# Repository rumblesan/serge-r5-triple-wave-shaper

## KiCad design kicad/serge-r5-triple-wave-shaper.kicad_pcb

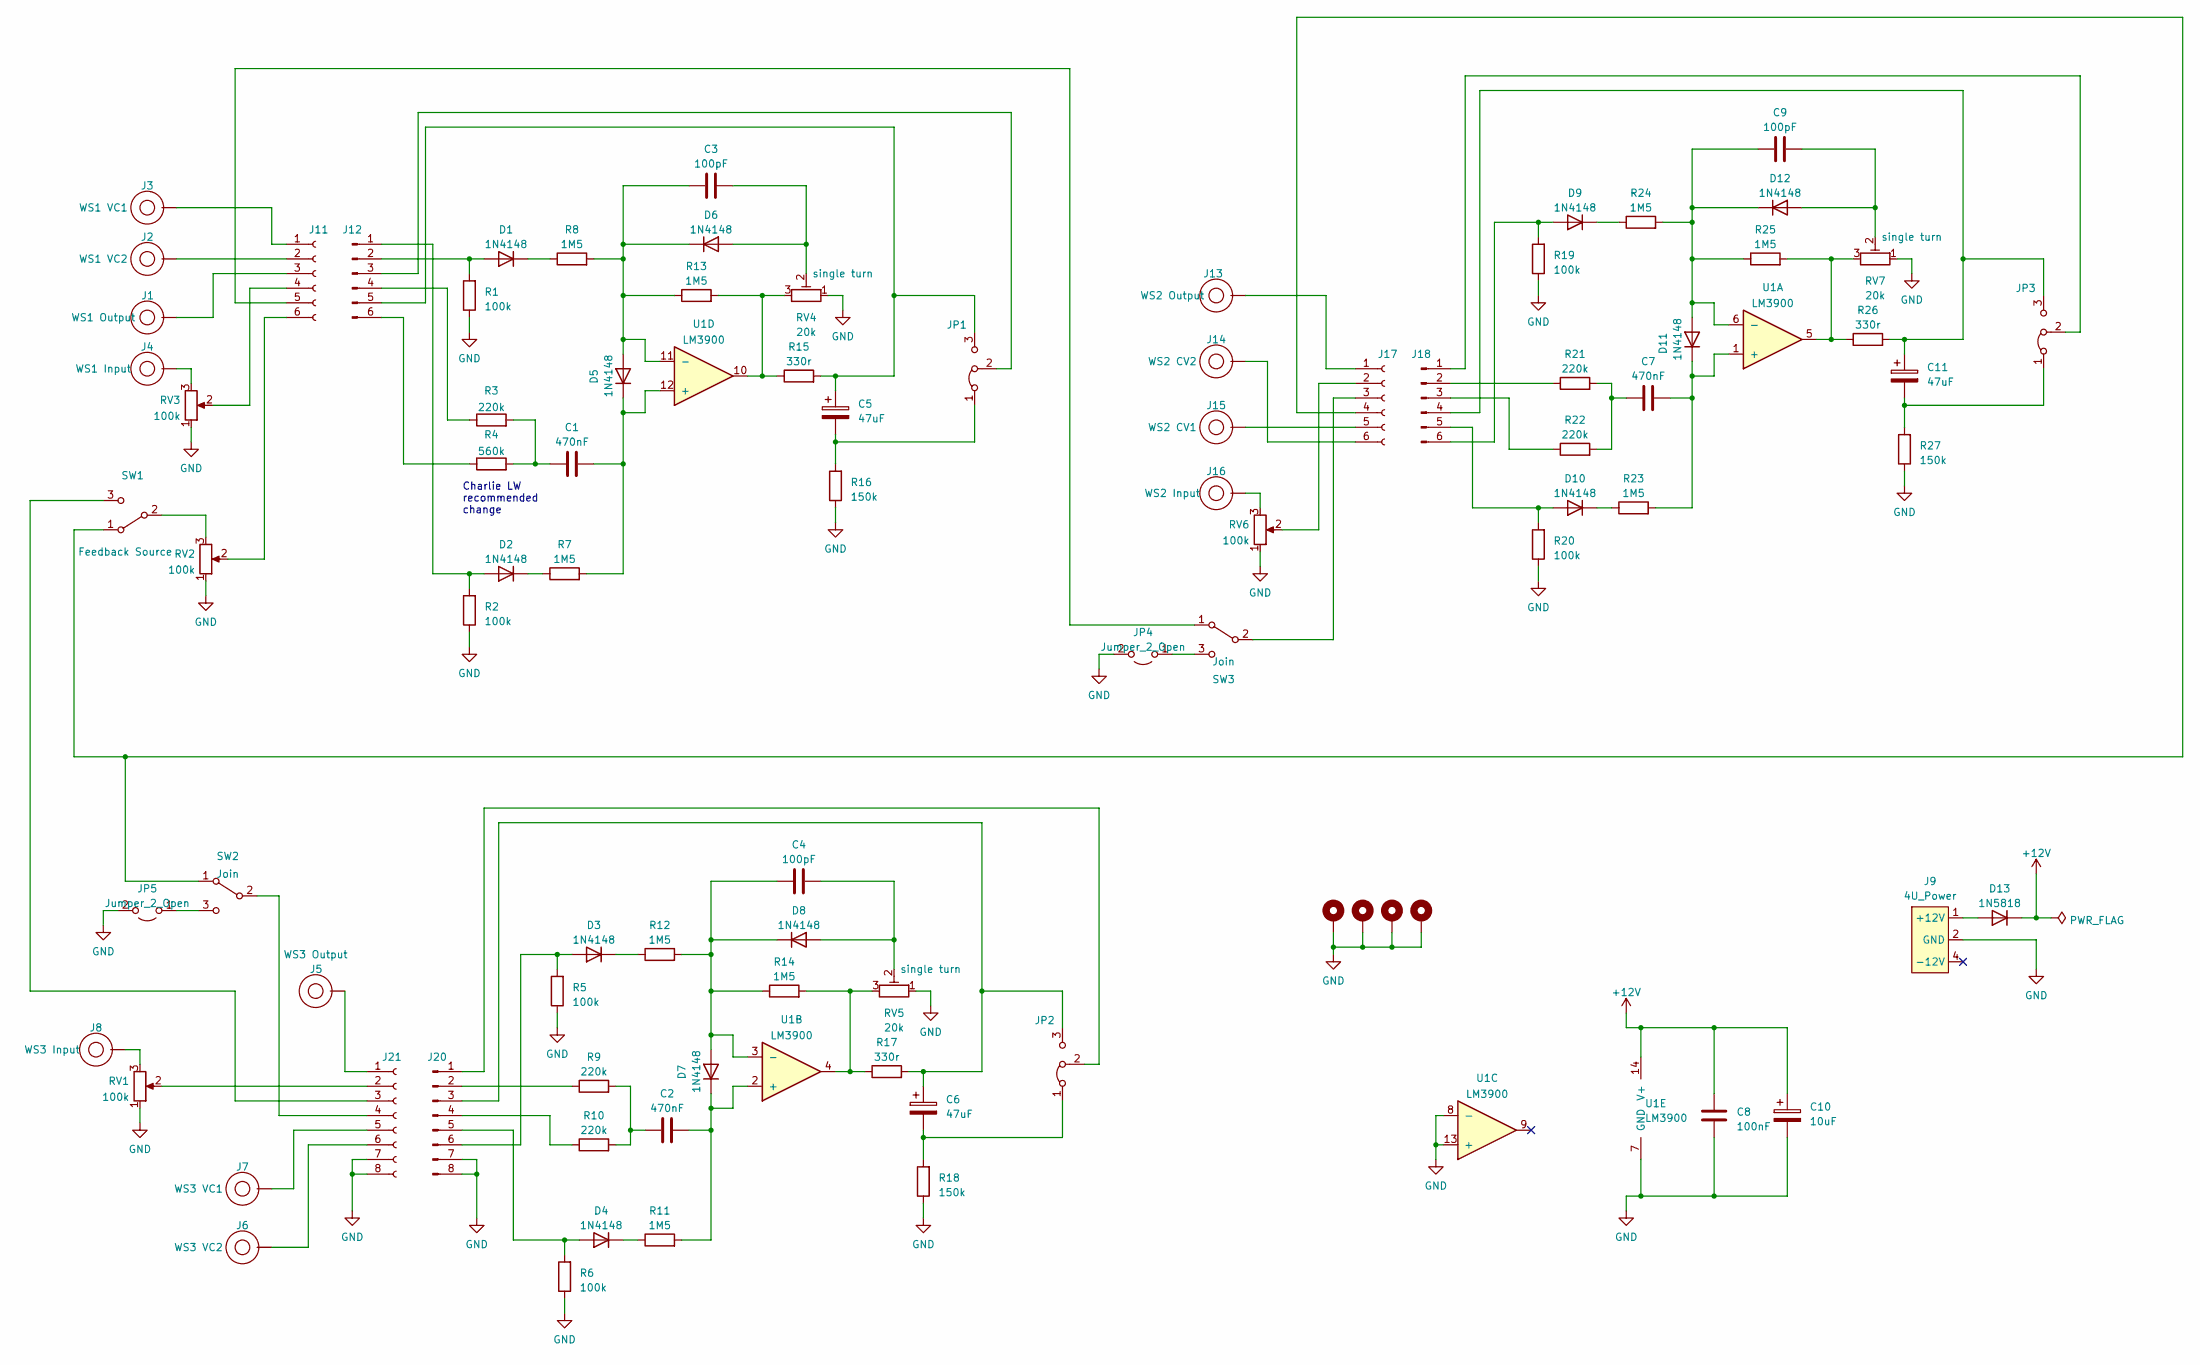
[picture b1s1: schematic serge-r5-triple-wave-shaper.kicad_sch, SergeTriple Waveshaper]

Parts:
C1, C2, C7: 470nF; C_Rect_L7.2mm_W8.5mm_P5.00mm_FKP2_FKP2_MKS2_MKP2; Tolerance 5%
C3, C4, C9: 100pF; C_Rect_L7.0mm_W3.5mm_P5.00mm; Tolerance 5%
C5, C6, C11: 47uF; CP_Radial_D5.0mm_P2.00mm; Tolerance 20%; Voltage 50v
C8: 100nF; C_Rect_L7.0mm_W3.5mm_P5.00mm; Tolerance 5%
C10: 10uF; CP_Radial_D5.0mm_P2.00mm; Tolerance 20%; Voltage 50v
D1, D2, D3, D4, D5, D6, D7, D8, D9, D10, D11, D12: 1N4148; D_DO-35_SOD27_P7.62mm_Horizontal
D13: 1N5818; D_DO-41_SOD81_P10.16mm_Horizontal
H1, H2, H3, H4: MountingHole_Pad; MountingHole_3.2mm_M3_Pad
J1, J2, J3, J4, J5, J6, J7, J8, J13, J14, J15, J16: Banana Socket PanelMount; BananaJack_THT_JohnsonCinch_108-09
J9: 4U_Power; 4u_Power_Molex_KK-254_P2.54mm
J11, J17: Conn_01x06_Female; PinSocket_1x06_P2.54mm_Vertical
J12, J18: Conn_01x06_Male; PinHeader_1x06_P2.54mm_Vertical
J20: Conn_01x08_Pin; PinHeader_1x08_P2.54mm_Vertical
J21: Conn_01x08_Socket; PinSocket_1x08_P2.54mm_Vertical
JP1, JP2, JP3: Jumper_3_Bridged12; PinHeader_1x03_P2.54mm_Vertical
JP4, JP5: Jumper_2_Open; SolderJumper-2_P1.3mm_Open_Pad1.0x1.5mm
R1, R2, R5, R6, R19, R20: 100k; R_Axial_DIN0207_L6.3mm_D2.5mm_P10.16mm_Horizontal; Tolerance 1%
R3, R9, R10, R21, R22: 220k; R_Axial_DIN0207_L6.3mm_D2.5mm_P10.16mm_Horizontal; Tolerance 1%
R4: 560k; R_Axial_DIN0207_L6.3mm_D2.5mm_P10.16mm_Horizontal; Tolerance 1%
R7, R8, R11, R12, R13, R14, R23, R24, R25: 1M5; R_Axial_DIN0207_L6.3mm_D2.5mm_P10.16mm_Horizontal; Tolerance 1%
R15, R17, R26: 330r; R_Axial_DIN0207_L6.3mm_D2.5mm_P10.16mm_Horizontal; Tolerance 1%
R16, R18, R27: 150k; R_Axial_DIN0207_L6.3mm_D2.5mm_P10.16mm_Horizontal; Tolerance 1%
RV1, RV2, RV3, RV6: 100k; Potentiometer_Alpha_RD901F-40-00D_Single_Vertical
RV4, RV5, RV7: 20k; Potentiometer_THT_Bourns_3306P_Vertical
SW1, SW2, SW3: SW_SPDT; Toggle_Switch_100SP-M2
U1: LM3900; DIP-14_W7.62mm_Socket

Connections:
+12V: C8.1, C10.1, D13.1 (K), U1.14 (V+)
GND: C8.2, C10.2, H1.1, H2.1, H3.1, H4.1, J9.2 (GND), J9.3 (GND), J20.7, J20.8, J21.7, J21.8, JP4.2 (B), JP5.2 (B), R1.1, R2.1, R5.1, R6.1, R16.1, R18.1, R19.1, R20.1, R27.1, RV1.1, RV2.1, RV3.1, RV4.1, RV5.1, RV6.1, RV7.1, U1.7 (GND), U1.8 (-), U1.13 (+)
unnamed: C1.1, R3.2, R4.2
unnamed: C2.1, R9.2, R10.2
unnamed: C7.1, R21.2, R22.2
unnamed: D1.2 (A), J12.2, R1.2
unnamed: D1.1 (K), R8.1
unnamed: D2.2 (A), J12.1, R2.2
unnamed: D2.1 (K), R7.1
unnamed: D3.2 (A), J20.6, R5.2
unnamed: D3.1 (K), R12.1
unnamed: D4.2 (A), J20.5, R6.2
unnamed: D4.1 (K), R11.1
unnamed: C3.1, D5.2 (A), D6.1 (K), R8.2, R13.1, U1.11 (-)
unnamed: C1.2, D5.1 (K), R7.2, U1.12 (+)
unnamed: C3.2, D6.2 (A), RV4.2
unnamed: C4.1, D7.2 (A), D8.1 (K), R12.2, R14.1, U1.3 (-)
unnamed: C2.2, D7.1 (K), R11.2, U1.2 (+)
unnamed: C4.2, D8.2 (A), RV5.2
unnamed: D9.2 (A), J18.6, R19.2
unnamed: D9.1 (K), R24.1
unnamed: D10.2 (A), J18.5, R20.2
unnamed: D10.1 (K), R23.1
unnamed: C9.1, D11.2 (A), D12.1 (K), R24.2, R25.1, U1.6 (-)
unnamed: C7.2, D11.1 (K), R23.2, U1.1 (+)
unnamed: C9.2, D12.2 (A), RV7.2
unnamed: D13.2 (A), J9.1 (+12V)
unnamed: J4.1, RV3.3
unnamed: J8.1, RV1.3
unnamed: J3.1, J11.1
unnamed: J2.1, J11.2
unnamed: J1.1, J11.3
unnamed: J11.4, RV3.2
unnamed: J11.5, SW3.1 (A)
unnamed: J11.6, RV2.2
unnamed: J12.3, JP1.2 (C)
unnamed: J12.4, R3.1
unnamed: C5.1, J12.5, JP1.3 (B), R15.2
unnamed: J12.6, R4.1
unnamed: J16.1, RV6.3
unnamed: J13.1, J17.1
unnamed: J17.2, RV6.2
unnamed: J17.3, SW3.2 (B)
unnamed: J17.4, SW1.1 (A), SW2.1 (A)
unnamed: J15.1, J17.5
unnamed: J14.1, J17.6
unnamed: J18.1, JP3.2 (C)
unnamed: J18.2, R21.1
unnamed: J18.3, R22.1
unnamed: C11.1, J18.4, JP3.3 (B), R26.2
unnamed: J20.1, JP2.2 (C)
unnamed: J20.2, R9.1
unnamed: C6.1, J20.3, JP2.3 (B), R17.2
unnamed: J20.4, R10.1
unnamed: J5.1, J21.1
unnamed: J21.2, RV1.2
unnamed: J21.3, SW1.3 (C)
unnamed: J21.4, SW2.2 (B)
unnamed: J7.1, J21.5
unnamed: J6.1, J21.6
unnamed: C5.2, JP1.1 (A), R16.2
unnamed: C6.2, JP2.1 (A), R18.2
unnamed: C11.2, JP3.1 (A), R27.2
unnamed: JP4.1 (A), SW3.3 (C)
unnamed: JP5.1 (A), SW2.3 (C)
unnamed: R13.2, R15.1, RV4.3, U1.10
unnamed: R14.2, R17.1, RV5.3, U1.4
unnamed: R25.2, R26.1, RV7.3, U1.5
unnamed: RV2.3, SW1.2 (B)

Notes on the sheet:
Charlie LW recommended change

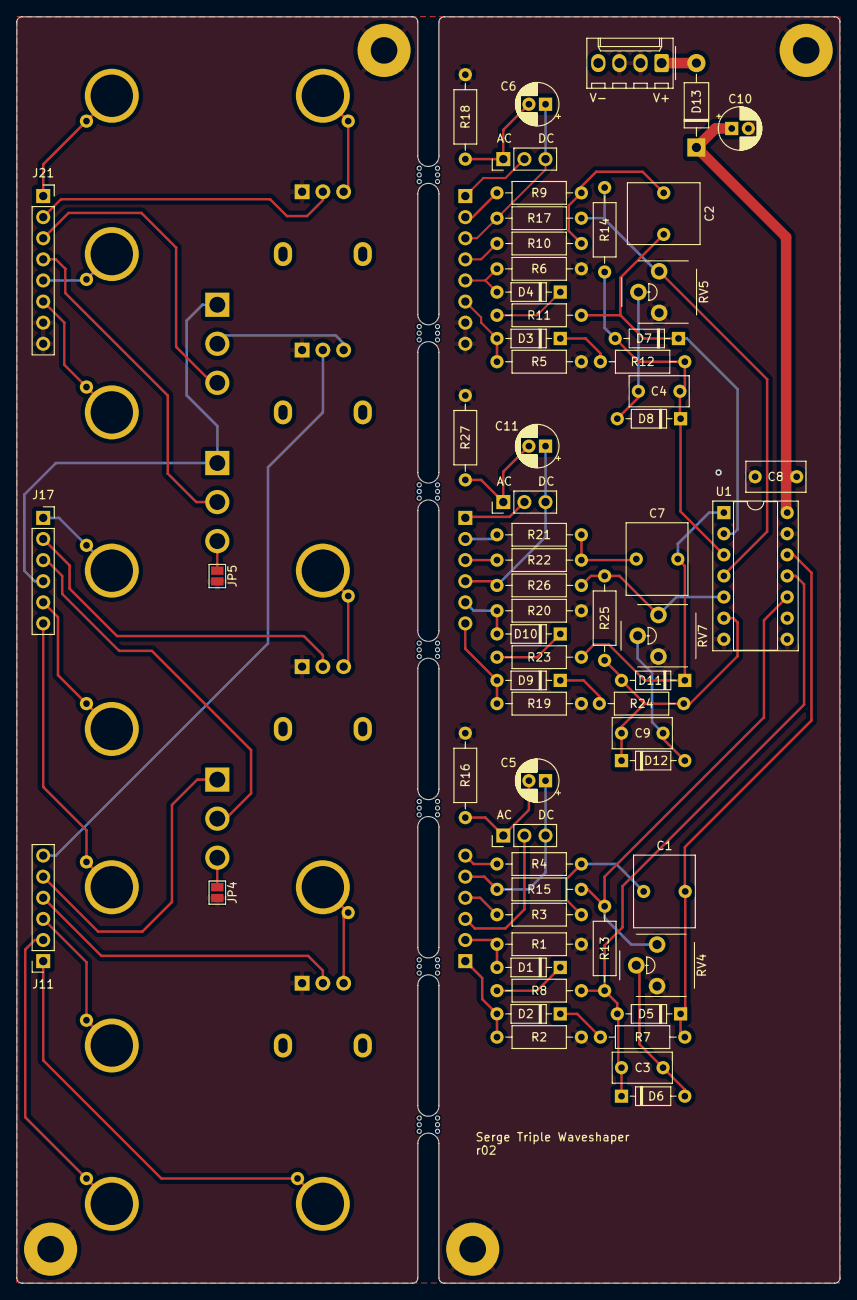
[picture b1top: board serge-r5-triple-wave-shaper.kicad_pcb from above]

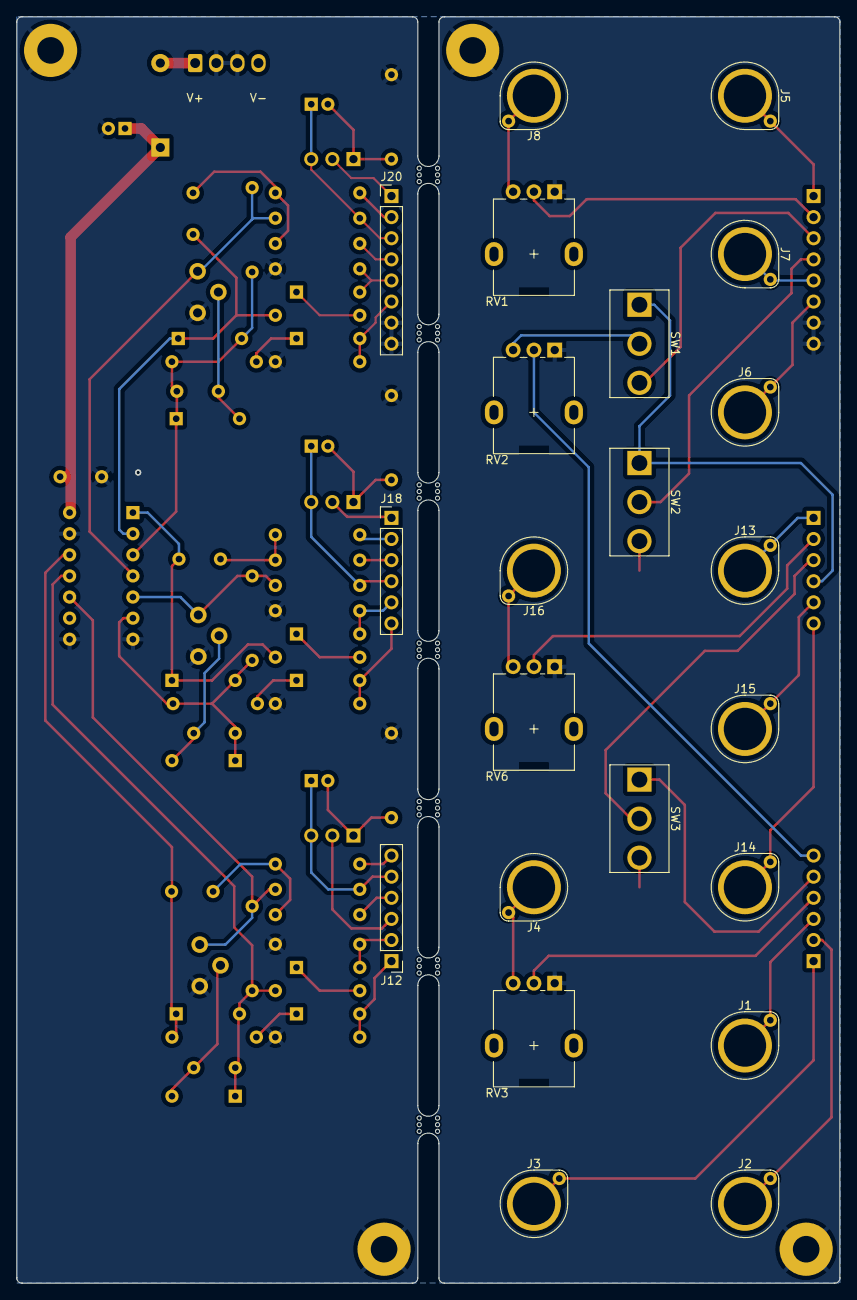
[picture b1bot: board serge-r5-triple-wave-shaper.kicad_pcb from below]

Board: 2 copper layers, 99.1 x 152.4 mm, 97 parts (22 on the bottom side), 69 nets.

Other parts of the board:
mouse-bite-2.54mm-slot, mouse-bite-2.54mm-slot#2, mouse-bite-2.54mm-slot#3, mouse-bite-2.54mm-slot#4, mouse-bite-2.54mm-slot#5, mouse-bite-2.54mm-slot#6, mouse-bite-2.54mm-slot#7: VAL**; mouse-bite-2.54mm-slot

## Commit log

2023-10-09 Moving this into its own repo and fixing bugs
2023-10-21 Regenerate gerbers after tweaks
2023-11-11 Adding ibom
